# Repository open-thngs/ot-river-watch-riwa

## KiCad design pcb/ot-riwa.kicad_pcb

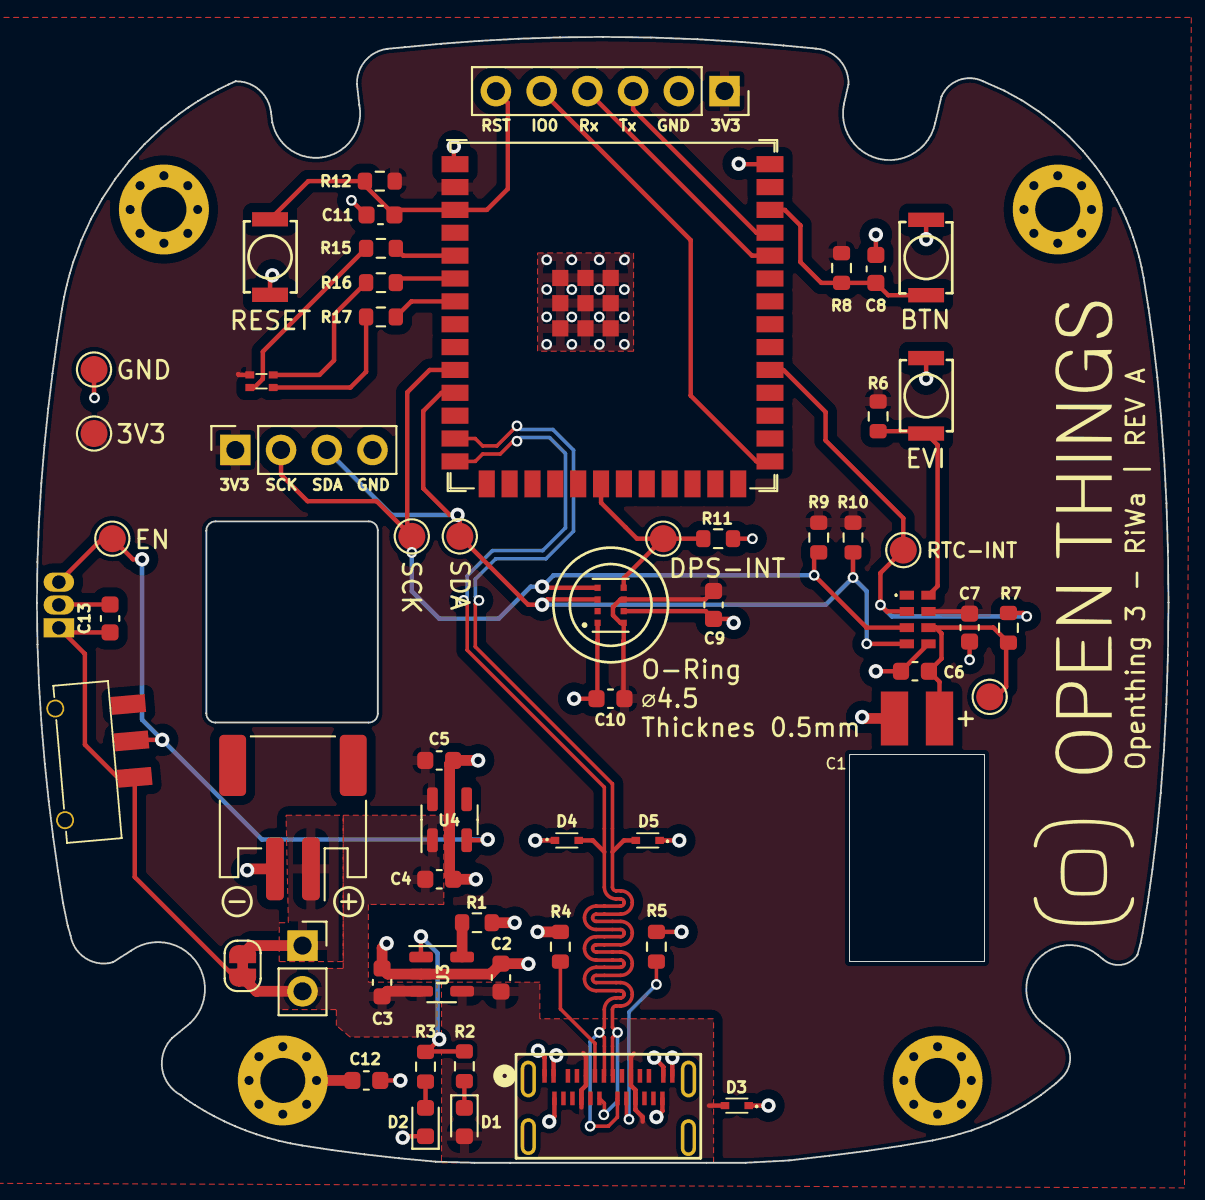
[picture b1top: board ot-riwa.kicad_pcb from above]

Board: 2 copper layers, 62.9 x 62.5 mm, 63 parts (1 on the bottom side), 32 nets.

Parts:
BT1: Battery_Cell; JST_PH_S2B-PH-SM4-TB_1x02-1MP_P2.00mm_Horizontal
C1: JUWT1105MCD; supercap_horizontal
C2, C3: 10uF; C_0603_1608Metric
C4, C5: 1uF; C_0603_1608Metric
C6, C7, C8, C9, C10, C11, C12, C13: 0.1uF; C_0603_1608Metric
D1: LED_RED; LED_0603_1608Metric
D2: LED_GREEN; LED_0603_1608Metric
D3, D4, D5: LESD5D5.0CT1G; LESD5D50CT1G
G1: LOGO
H1, H2, H3, H4: MountingHole_Pad; MountingHole_2.5mm_Pad_Via
IC1: RV-3028-C7; RV3028C732768kHz1ppmTAQC
IC2: DRV5032FB; DRV5032DULPGM
J1: 124018612112A; CONN_124018612112A_AMP
J2: DNP; PinSocket_1x02_P2.54mm_Vertical
J3: DNP; PinSocket_1x06_P2.54mm_Vertical
J4: Conn_01x04_Pin; PinSocket_1x04_P2.54mm_Vertical
JP1: DNP; SolderJumper-2_P1.3mm_Bridged_RoundedPad1.0x1.5mm
LED1: APHF1608LSEEQBDZGKC
R1: 2k; R_0603_1608Metric
R2, R3: 1k; R_0603_1608Metric
R4, R5: 5k1; R_0603_1608Metric
R6, R7, R8, R9, R10, R11, R12: 10k; R_0603_1608Metric
R15: 1k2; R_0603_1608Metric
R16: 2k2; R_0603_1608Metric
R17: 390R; R_0603_1608Metric
SW1, SW2, SW3: SKRKAEE020
TP1: TP_3V3; TestPoint_Pad_D1.5mm
TP2: TP_GND; TestPoint_Pad_D1.5mm
TP3: TP_SDA; TestPoint_Pad_D1.5mm
TP4: TP_SCK; TestPoint_Pad_D1.5mm
TP5: TP_RTC_INT; TestPoint_Pad_D1.5mm
TP6: TP_DPS_INT; TestPoint_Pad_D1.5mm
TP7: TP_VBACKUP; TestPoint_Pad_D1.5mm
TP8: TP_ENABLE; TestPoint_Pad_D1.5mm
U1: DPS368XTSA1; XDCR_DPS368XTSA1
U3: MCP73831/OT; SOT-23-5
U4: AP2112K-3.3; SOT-23-5
U5: 450405020524
U6: ESP32-S3-WROOM-1; ESP32-S3-WROOM-1U

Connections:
+3.3V: C5.1, C7.1, C9.1, C10.1, IC1.7 (VDD), J3.1, J4.1, LED1.1 (A), R6.1, R8.1, R9.2, R10.2, R12.1, TP1.1, U1.6 (VDDIO), U1.8 (VDD), U4.5 (VOUT), U6.2 (3V3)
+BATT: C3.1, C4.1, C13.1, IC2.1 (VCC), J2.2, JP1.2 (B), U3.3 (V_{BAT}), U4.1 (VIN), U5.3 (COM)
/main/DPS_INT: R11.1, TP6.1, U1.5 (SDO), U6.20 (GPIO12/TOUCH12/ADC2_CH1/FSPICLK/FSPIIO6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)
/main/MCU/BTN: C8.1, R8.2, SW2.1, U6.38 (GPIO2/TOUCH2/ADC1_CH1)
/main/MCU/GPIO0: J3.5, U6.27 (GPIO0/BOOT)
/main/MCU/LED_BLUE: R17.1, U6.7 (GPIO7/TOUCH7/ADC1_CH6)
/main/MCU/LED_GREEN: R16.1, U6.6 (GPIO6/TOUCH6/ADC1_CH5)
/main/MCU/LED_RED: R15.2, U6.5 (GPIO5/TOUCH5/ADC1_CH4)
/main/MCU/RESET: C11.1, J3.6, R12.2, SW3.1, U6.3 (EN)
/main/MCU/Rx: J3.4, U6.36 (U0RXD/GPIO44/CLK_OUT2)
/main/MCU/Tx: J3.3, U6.37 (U0TXD/GPIO43/CLK_OUT1)
/main/MCU/USB_D+: D4.2 (A2), J1.A6 (D1+), J1.B6 (D2+), U6.14 (GPIO20/U1CTS/ADC2_CH9/CLK_OUT1/USB_D+)
/main/MCU/USB_D-: D5.2 (A2), J1.A7 (D1-), J1.B7 (D2-), U6.13 (GPIO19/U1RTS/ADC2_CH8/CLK_OUT2/USB_D-)
/main/PSU/BATTX+: BT1.1 (+), J2.1, JP1.1 (A)
/main/PSU/ENABLE: IC2.3 (OUT2), TP8.1, U4.3 (EN), U5.2 (OUT2)
/main/RTC/EVI: IC1.8 (EVI), R6.2, SW1.2
/main/RTC/VBackup: C1.1 (+), C6.1, IC1.6 (VBACKUP), R7.2, TP7.1
/main/SCK: IC1.3 (SCL), J4.2, R9.1, TP4.1, U1.4 (SCK), U6.10 (GPIO17/U1TXD/ADC2_CH6)
/main/SDA: IC1.4 (SDA), J4.3, R10.1, TP3.1, U1.3 (SDI), U6.11 (GPIO18/U1RXD/ADC2_CH7/CLK_OUT3)
/main/~RTC_INT: IC1.2 (~INT), R7.1, TP5.1, U6.31 (GPIO38/FSPIWP/SUBSPIWP)
GND: BT1.2 (-), C1.2 (-), C2.2, C3.2, C4.2, C5.2, C6.2, C7.2, C8.2, C9.2, C10.2, C11.2, C12.2, C13.2, D2.1 (K), D3.1 (A1), D4.1 (A1), D5.1 (A1), IC1.5 (VSS), IC2.2 (GND), J1.25 (GND), J1.26 (GND), J1.A1 (GND_A), J1.A12 (GND_A), J1.B1 (GND_B), J1.B12 (GND_B), J3.2, J4.4, R1.2, R4.1, R5.1, R11.2, SW1.1, SW2.2, SW3.2, TP2.1, U1.1 (GND), U1.7 (GND), U3.2 (V_{SS}), U4.2 (GND), U6.1 (GND), U6.40 (GND), U6.41 (GND)
unnamed: C12.1, H1.1
unnamed: D1.1 (K), R2.2
unnamed: D2.2 (A), R3.2
unnamed: J1.A5 (CC1), R4.2
unnamed: J1.B5 (CC2), R5.2
unnamed: LED1.3 (B), R17.2
unnamed: LED1.4 (G), R16.2
unnamed: LED1.2 (R), R15.1
unnamed: R1.1, U3.5 (PROG)
unnamed: R2.1, R3.1, U3.1 (STAT)
VBUS: C2.1, D1.2 (A), D3.2 (A2), J1.A4 (VBUS_A), J1.A9 (VBUS_A), J1.B4 (VBUS_B), J1.B9 (VBUS_B), U3.4 (V_{DD})

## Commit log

2023-07-24 Added calculations for accurate height
2023-07-24 added sea level height measurment
2023-08-07 Added template project structure
2023-08-11 Added first components
2023-08-14 Placed components on PCB Board (no layouting)
2024-02-15 Modified code and implemented ESPNow variant with ESP32
2024-02-15 Added some images
2024-02-15 Replaces nRF52840 with ESP32-S3
2024-02-16 Layout all components
2024-02-21 Refactored layout + silkscreen + added I2C connector
2024-02-21 Changed kibot yml to find actual pcb file
2024-02-21 Try to change push pull kibot trigger
2024-02-21 try again
2024-02-21 Added actual KiBot actions to the yml file
2024-02-21 Try to change upload and checkout to use latest versions
2024-02-21 Use version v4
2024-03-07 Refactored components
2024-03-15 Fixed usage of strapping pins
2024-03-18 Add readme for toit code
2024-03-18 Add test for i2c scan and rgb led
2024-03-21 Refactored code + fixed rgb-led code to show actual colors
2024-03-23 Added minimal espnow test programms for bouy and station for testing
2024-03-23 Implemented RTC usage and sync to synchronize both devices
2024-03-27 modified toit code to run permanently
2024-11-06 Implement RTC and device sync + updated 3d objects
2024-11-06 Add Fleet information (no wifi)
